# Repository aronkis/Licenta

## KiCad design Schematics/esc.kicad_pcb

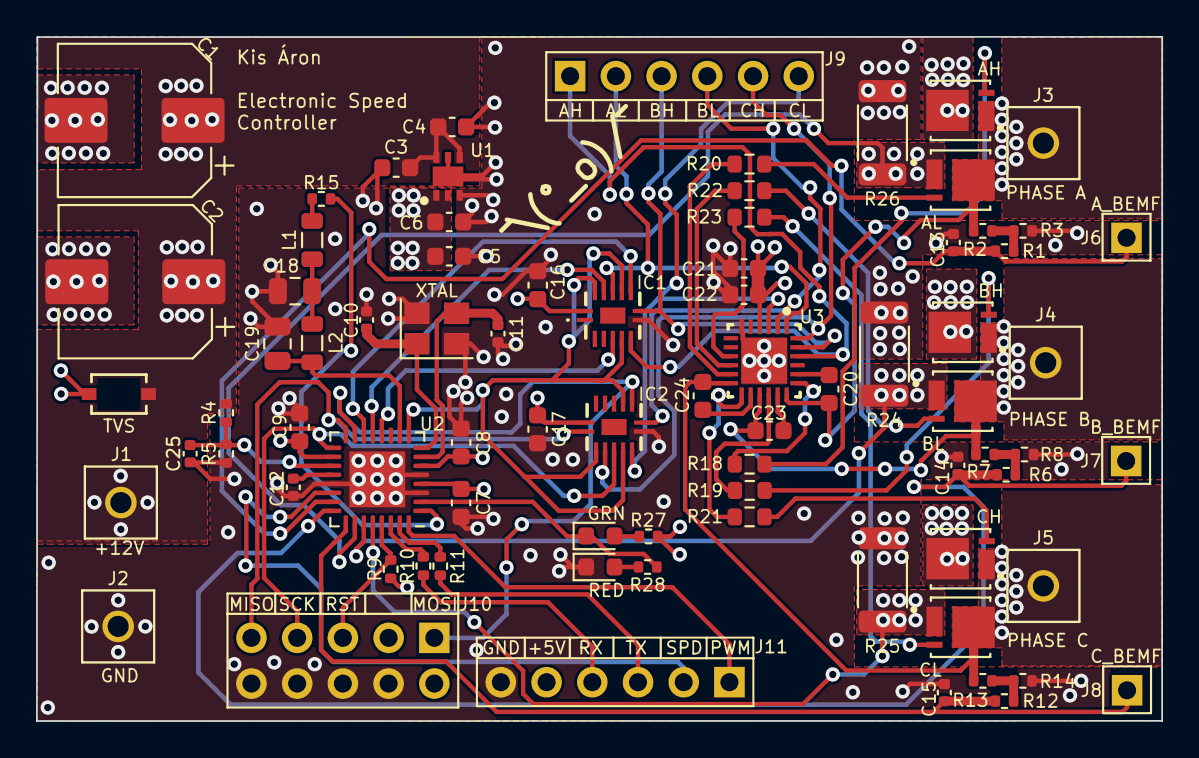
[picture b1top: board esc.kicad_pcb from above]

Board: 4 copper layers, 62.5 x 38.0 mm, 79 parts (0 on the bottom side), 61 nets.

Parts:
AH: BSZ0902NS
AL: BSZ0902NS
BH: BSZ0902NS
BL: BSZ0902NS
C1, C2: 470u; CP_Elec_8x10
C3, C4, C22: 1u; C_0603_1608Metric
C5, C6: 2.2u; C_0603_1608Metric
C7, C8, C9, C16, C17: 100n; C_0603_1608Metric
C10, C11: 22p; C_0402_1005Metric
C12, C25: 100n; C_0402_1005Metric
C13, C14, C15: 2.2n; C_0402_1005Metric
C18, C19: 47uF; C_0805_2012Metric
C20, C21, C23, C24: 0.1u; C_0603_1608Metric
CH: BSZ0902NS
CL: BSZ0902NS
GRN: LED; LED_0603_1608Metric
IC1, IC2: 74HCT08BQ,115; 74HCT08BQ115
J1, J2, J3, J4, J5: 8730
J6, J7, J8: Conn_01x01; PinHeader_1x01_P2.54mm_Vertical
J9, J11: Conn_01x06; PinHeader_1x06_P2.54mm_Vertical
J10: AVR-ISP-10; PinHeader_2x05_P2.54mm_Vertical
L1, L2: 100uH; L_0805_2012Metric
R1, R6, R9, R12: 10k; R_0402_1005Metric
R2, R4, R7, R13: 33k; R_0402_1005Metric
R3, R8, R14: 20k; R_0402_1005Metric
R5: 7.5k; R_0402_1005Metric
R10, R11: 1k; R_0402_1005Metric
R15: 30; R_0402_1005Metric
R18, R19, R20, R21, R22, R23: 15; R_0603_1608Metric
R24, R25, R26: 5m; R_2010_5025Metric
R27, R28: 300; R_0402_1005Metric
RED: LED; LED_0603_1608Metric
TVS: PTVS12VS1UTR_115; CR_1UTR_115_NEX
U1: TLV76750DRVx; SON65P200X200X80-7N
U2: ATmega328P-M; QFN-32-1EP_5x5mm_P0.5mm_EP3.1x3.1mm
U3: DRV8300DRGER; RGE0024B-IPC_C
XTAL: ECS-80-12-33-JGN-TR; Crystal_SMD_3225-4Pin_3.2x2.5mm

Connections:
+5V: C5.2, C6.2, C7.2, C8.2, C9.2, C16.1, C17.1, IC1.14 (VCC), IC2.14 (VCC), J10.2 (VCC), J11.5, R9.1, R27.1, U1.1 (OUT), U1.2 (SNS), U2.4 (VCC), U2.6 (VCC), U2.18 (AVCC)
+12V: AH.5_6_7_8, BH.5_6_7_8, C1.1, C2.1, C3.2, C4.2, C21.1, C22.2, CH.5_6_7_8, J1.1, R4.2, TVS.1, U1.4 (EN), U1.6 (IN), U3.4 (GVDD)
AH: IC1.4 (2A), U2.12 (PB0)
AH_PWM: IC1.6 (2Y), J9.1, U3.22 (INHA)
AL: IC1.12 (4A), U2.13 (PB1)
AL_PWM: IC1.11 (4Y), J9.2, U3.1 (INLA)
BH: IC1.9 (3A), U2.14 (PB2)
BH_PWM: IC1.8 (3Y), J9.3, U3.23 (INHB)
BL: IC2.9 (3A), J10.1 (MOSI), U2.15 (PB3)
BL_PWM: IC2.8 (3Y), J9.4, U3.2 (INLB)
CH: IC2.1 (1A), J10.9 (MISO), U2.16 (PB4)
CH_PWM: IC2.3 (1Y), J9.5, U3.24 (INHC)
CL: IC2.4 (2A), J10.7 (SCK), U2.17 (PB5)
CL_PWM: IC2.6 (2Y), J9.6, U3.3 (INLC)
COIL_A: AH.1_2_3, AL.5_6_7_8, C20.1, J3.1, R2.1, U3.18 (SHA)
COIL_A_BEMF: C13.2, J6.1, R1.1, U2.23 (PC0)
COIL_A_CURR: AL.1_2_3, R26.2, U2.26 (PC3)
COIL_B: BH.1_2_3, BL.5_6_7_8, C23.1, J4.1, R7.1, U3.15 (SHB)
COIL_B_BEMF: C14.2, J7.1, R6.1, U2.24 (PC1)
COIL_B_CURR: BL.1_2_3, R24.2, U2.27 (PC4)
COIL_C: C24.1, CH.1_2_3, CL.5_6_7_8, J5.1, R13.1, U3.12 (SHC)
COIL_C_BEMF: C15.2, J8.1, R12.1, U2.25 (PC2)
COIL_C_CURR: CL.1_2_3, R25.2, U2.28 (PC5)
COMP_REF_IN: C19.2, L2.2, U2.10 (PD6)
COMP_REF_OUT: R15.2, U2.1 (PD3)
GND: C1.2, C2.2, C3.1, C4.1, C5.1, C6.1, C7.1, C8.1, C9.1, C10.1, C11.1, C12.1, C13.1, C14.1, C15.1, C16.2, C17.2, C18.1, C19.1, C21.2, C22.1, C25.1, IC1.7 (GND_1), IC2.7 (GND_1), J2.1, J10.4 (GND), J10.6 (GND), J10.8 (GND), J10.10 (GND), J11.6, R3.1, R5.1, R8.1, R14.1, R24.1, R25.1, R26.1, RED.1 (K), TVS.2, U1.3 (GND), U1.5 (GND), U1.7 (PAD), U2.3 (GND), U2.5 (GND), U2.21 (GND), U2.33 (GND), U3.6 (GND), U3.25 (PowerPAD), XTAL.2, XTAL.4
LED: GRN.1 (K), R28.1, U2.2 (PD4)
unnamed: AH.4, R18.2
unnamed: AL.4, R20.2
unnamed: BH.4, R19.2
unnamed: BL.4, R22.2
unnamed: C18.2, L1.2, L2.1
unnamed: CH.4, R21.2
unnamed: CL.4, R23.2
unnamed: GRN.2 (A), R27.2
unnamed: L1.1, R15.1
unnamed: R1.2, R2.2, R3.2
unnamed: R6.2, R7.2, R8.2
unnamed: R12.2, R13.2, R14.2
unnamed: R28.2, RED.2 (A)
unnamed: C12.2, U2.20 (AREF)
unnamed: R10.2, U2.30 (PD0)
unnamed: R11.2, U2.31 (PD1)
unnamed: C20.2, U3.20 (BSTA)
unnamed: C23.2, U3.17 (BSTB)
unnamed: C24.2, U3.14 (BSTC)
unnamed: R18.1, U3.19 (GHA)
unnamed: R19.1, U3.16 (GHB)
unnamed: R21.1, U3.13 (GHC)
unnamed: R20.1, U3.11 (GLA)
unnamed: R22.1, U3.10 (GLB)
unnamed: R23.1, U3.9 (GLC)
PWM_IN: J11.1, U2.32 (PD2)
PWM_OUT: IC1.5 (2B), IC1.10 (3B), IC1.13 (4B), IC2.2 (1B), IC2.5 (2B), IC2.10 (3B), U2.9 (PD5)
RST: J10.5 (~RST), R9.2, U2.29 (~RESET/PC6)
RX: J11.4, R10.1
SPEED_REF: J11.2, U2.22 (ADC7)
TX: J11.3, R11.1
VBUS: C25.2, R4.1, R5.2, U2.19 (ADC6)
XTAL1: C11.2, U2.7 (XTAL1/PB6), XTAL.3
XTAL2: C10.2, U2.8 (XTAL2/PB7), XTAL.1

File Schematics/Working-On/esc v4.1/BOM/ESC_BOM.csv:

"Reference","Value","Datasheet","Footprint","Qty","DNP"
"8MHz1","ECS-80-12-33-JGN-TR","ECS-80-12-30BQ-JES-TR","Crystal:Crystal_SMD_3225-4Pin_3.2x2.5mm","1",""
"C1,C2","470u","~","Capacitor_SMD:CP_Elec_8x10","2",""
"C3,C4,C22","1u","~","Capacitor_SMD:C_0603_1608Metric","3",""
"C5,C6","2.2u","~","Capacitor_SMD:C_0603_1608Metric","2",""
"C7,C8,C9,C12,C16,C17","100n","~","-- mixed values --","6",""
"C10,C11","22p","~","Capacitor_SMD:C_0402_1005Metric","2",""
"C13,C14,C15","2.4n","~","Capacitor_SMD:C_0402_1005Metric","3",""
"C18,C19","47uF","~","Capacitor_SMD:C_0805_2012Metric","2",""
"C20,C21,C23,C24","0.1u","~","Capacitor_SMD:C_0603_1608Metric","4",""
"GRN1,RED1","LED","~","LED_SMD:LED_0603_1608Metric","2",""
"IC1,IC2","74HCT08BQ,115","https://assets.nexperia.com/documents/data-sheet/74HC_HCT08.pdf","74HCT08BQ115:74HCT08BQ115","2",""
"J1,J2,J3,J4,J5","8730","","8730:8730","5",""
"J6,J7,J8","Conn_01x01","~","Connector_PinHeader_1.00mm:PinHeader_1x01_P1.00mm_Vertical","3",""
"J9,J11","Conn_01x06","~","Connector_PinHeader_2.54mm:PinHeader_1x06_P2.54mm_Vertical","2",""
"J10","AVR-ISP-10"," ~","Connector_PinHeader_2.54mm:PinHeader_2x05_P2.54mm_Vertical","1",""
"L1,L2","100uH","~","Inductor_SMD:L_0805_2012Metric","2",""
"Q1,Q2,Q3,Q4,Q5,Q6","BSZ0902NS","","BSZ0902NS:BSZ0902NS","6",""
"R1,R3,R5,R6,R8,R9,R12,R14","10k","~","Resistor_SMD:R_0402_1005Metric","8",""
"R2,R4,R7,R13","33k","~","Resistor_SMD:R_0402_1005Metric","4",""
"R10,R11","1k","~","Resistor_SMD:R_0402_1005Metric","2",""
"R15","30","~","Resistor_SMD:R_0402_1005Metric","1",""
"R16,R17","300","~","Resistor_SMD:R_0402_1005Metric","2",""
"R18,R19,R20,R21,R22,R23","15","~","Resistor_SMD:R_0603_1608Metric","6",""
"R24,R25,R26","5m","~","Resistor_SMD:R_2010_5025Metric","3",""
"TVS1","PTVS12VS1UTR_115","PTVS12VS1UTR_115","PTVS12VS1UTR-115:CR_1UTR_115_NEX","1",""
"U1","TLV76750DRVx","www.ti.com/lit/gpn/TLV767","TLV76750DRVR:SON65P200X200X80-7N","1",""
"U2","ATmega328P-M","http://ww1.microchip.com/downloads/en/DeviceDoc/ATmega328_P%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","Package_DFN_QFN:QFN-32-1EP_5x5mm_P0.5mm_EP3.1x3.1mm","1",""
"U3","DRV8300DRGER","DRV8300DRGER","DRV8300DRGER:RGE0024B-IPC_C","1",""

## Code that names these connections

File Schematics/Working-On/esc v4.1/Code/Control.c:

#include "Arduino.h"

const uint8_t max_pwm_adr = 0x00;
const uint8_t min_pwm_adr = 0x02;

const uint8_t pwm_start_value = 35;
const uint8_t pwm_min_value = 35;
const uint8_t pwm_max_value = 255;
uint8_t motor_speed = 0;
uint8_t pwm_pin_change = 0;


uint64_t pwm_end = 0;
uint64_t pwm_start = 0;

const uint16_t min_pwm = 1000;
const uint16_t max_pwm = 2000;
uint16_t motor_off_timer = 1000;
uint16_t pwm_input = 550;
uint16_t soft_start_timer = 2200;

static bool motor_enabled = false;
static uint8_t sequence_step = 0;

void setup()
{  
  // The pins for the MOSFET drivers are PB1, PB2, PB3, PD2, PD3 and PD4
  DDRB  |= B00001110;           // Configure pins PB1, PB2, PB3 as output (CH, BH, AH)
  PORTB &= B00000000;           // Pins 0 to 7 set to LOW
  DDRD  |= B00011100;           // Configure pin PD2, PD3, PD4 as output (CL, BL, AL)
  PORTD &= B00000000;           // Pins 0 to 7 set to LOW

  // Timer0
  TCCR1A = 0;
  TCCR1B = 0x01; // no prescaling

  // Timer1
  TCCR2A = 0;
  TCCR2B = 0x01; // no prescaling

  // Comparator on pin PD6
  ACSR   = 0x10;             // enable comparator interrupt

  // Set PB0 (PWM in) to trigger interrupt (we use this to read PWM input)
  PCICR  |= (1 << PCIE0);    // enable PCMSK0 scan, PWM_IN (PB0), which is PCIE0 in PCICR register.                                           
  PCMSK0 |= (1 << PCINT0);   // Set pin PB0 to trigger an interrupt on state change. 

  // For the comparator to be functional the ADC has to be disabled.
  ADCSRA = (0 << ADEN);     // Disable the ADC
  ADCSRB = (1 << ACME);     // MUX select for negative input of comparator
}

void soft_start()
{
  set_pwm(pwm_start_value);
  soft_start_timer = 2000;

  while(soft_start_timer > 500) {
    delayMicroseconds(soft_start_timer);
    set_next_step();
    sequence_step++;
    sequence_step %= 6;
    soft_start_timer -= 10;
  }

  motor_speed = pwm_start_value;    //??
  ACSR |= 0x08;                    // Enable analog comparator interrupt 
}

void motor_stop()
{
  if(!motor_off_timer) // to assure that the motor doesn't stop immediately
  {
    motor_enabled = false;
    ACSR   = 0x10;            // Disable and clear (flag bit) analog comparator interrupt
    motor_off_timer = 1000;
    PORTD = B00000000;
    PORTB = B00000000;
    TCCR1A =  0;   
    TCCR2A =  0;            
  }
  motor_off_timer = motor_off_timer - 1;       
}

void loop() {
  // if the PWM input is higher than a given threshold we start the motor
  if(pwm_input > min_pwm + 40)
  {
    motor_enabled = true;    
    motor_off_timer = 1000;
  }

  if(motor_enabled)
  {  
    soft_start();
    while(motor_enabled) 
    {
      pwm_input = constrain(pwm_input, min_pwm, max_pwm);
      motor_speed = map(pwm_input, min_pwm, max_pwm, pwm_min_value, pwm_max_value);
      set_pwm(motor_speed);
      if(pwm_input < min_pwm) // stop the motor
      {
        motor_stop();
      }
    }
  } 
} 

// Setting the timers to the PWM value
void set_pwm(byte pwm_value){
  OCR1A  = pwm_value;                   // Set pin PB1 PWM duty cycle
  OCR1B  = pwm_value;                   // Set pin PB2 PWM duty cycle
  OCR2A  = pwm_value;                   // Set pin PB3 PWM duty cycle
}

// Detecting the 0 crossing on falling and rising edges.
void BEMF_A_RISING(){  
  ADMUX = 2;                // Select PC2 as comparator negative input
  ACSR |= 0x03;             // Set interrupt on rising edge*/
}

void BEMF_A_FALLING(){
  ADMUX = 2;                // Select PC2 as comparator negative input
  ACSR &= ~0x01;            // Set interrupt on falling edge*/
}

void BEMF_B_RISING(){
  ADMUX = 0;                // Select PC0 as comparator negative input
  ACSR |= 0x03;             // Set interrupt on rising edge
}

void BEMF_B_FALLING(){
  ADMUX = 0;                // Select PC0 as comparator negative input
  ACSR &= ~0x01;            // Set interrupt on falling edge*/
}

void BEMF_C_RISING(){
  ADMUX = 1;                // Select PC1 as comparator negative input
  ACSR |= 0x03;             // Set interrupt on rising edge
}

void BEMF_C_FALLING(){
  ADMUX = 1;                // Select PC1 as comparator negative input
  ACSR &= ~0x01;            // Set interrupt on falling edge
}

// ACO indicates the output of the comparator, when AIN0 (PD6 - Virtual 0) voltage is 
// higher than the negative pin voltage then the ACO bit is set, otherwise it is clear.
ISR (ANALOG_COMP_vect) {
  for(int i = 0; i < 10; i++) {
    if(sequence_step & 1)             // If step = odd (0001, 0011, 0101) 1, 3 or 5
    {
      if(!(ACSR & 0x20)) i -= 1;      // ACO = 0 (Analog Comparator Output = 0) -> BEMF > Virtual 0
    }
    else                              // else if step is 0, 2 or 4
    {
      if((ACSR & 0x20)) i -= 1;       // ACO = 1 (Analog Comparator Output = 1) -> BEMF < Virtual 0
    }
  }
  set_next_step();                    // set the next step of the sequence
  sequence_step++;                    // increment step by 1, next part of the sequence of 6
  sequence_step %= 6;                 // If step > 5 (equal to 6) then step = 0 and start over
}

void set_next_step(){        
  switch(sequence_step){
    case 0:
      AH_BL();
      BEMF_C_RISING();
      break;
    case 1:
      AH_CL();
      BEMF_B_FALLING();
      break;
    case 2:
      BH_CL();
      BEMF_A_RISING();
      break;
    case 3:
      BH_AL();
      BEMF_C_FALLING();
      break;
    case 4:
      CH_AL();
      BEMF_B_RISING();
      break;
    case 5:
      CH_BL();
      BEMF_A_FALLING();
      break;
  }
}

/*On each step we change the digital pins to be HIGH or LOW or to be PWM or no-PWM 
depending on which step of the sequence we are*/
void AH_BL(){
  PORTD  = B00001000;     
  TCCR1A =  0;         
  TCCR2A =  0x81;         // OC2A - compare match noninverting mode, downcounting, PWM 8-bit      
}

void AH_CL(){
  PORTD  = B00000100;      
  TCCR1A =  0;         
  TCCR2A =  0x81;         // OC2A - compare match noninverting mode, downcounting, PWM 8-bit      
}

void BH_CL(){
  PORTD  = B00000100;      
  TCCR2A =  0;            
  TCCR1A =  0x21;         // OC1B - compare match noninverting mode, downcounting, PWM 8-bit 
}

void BH_AL(){  
  PORTD  = B00010000;      
  TCCR2A =  0;                  
  TCCR1A =  0x21;         // OC1B - compare match noninverting mode, downcounting, PWM 8-bit 
}

void CH_AL(){ 
  PORTD  = B00010000;       
  TCCR2A =  0;          
  TCCR1A =  0x81;         // OC1A - compare match noninverting mode, downcounting, PWM 8-bit 
}

void CH_BL(){  
  PORTD  = B00001000;        
  TCCR2A =  0;             
  TCCR1A =  0x81;         // OC1A - compare match noninverting mode, downcounting, PWM 8-bit
}

/* This is the interruption routine on pin change
   in this case for digital pin PB0 which is the PWM input */
ISR(PCINT0_vect){
  // First we take the current time in micro seconds using the micros() function
  pwm_end = micros();

  if(PINB & 0x01){                                   // We make an AND with the pin state register, We verify if pin 8 is HIGH
    if(pwm_pin_change == 0){                         // If the last state was 0, then we have a state change...
      pwm_pin_change = 1;                            // Store the current state into the last state for the next loop
      pwm_start = pwm_end;                           // Set counter_1 to current value.
    }
  }
  else if(pwm_pin_change == 1){                      // If pin PB0 is LOW and the last state was HIGH then we have a state change      
    pwm_pin_change = 0;                              // Store the current state into the last state for the next loop
    pwm_input = pwm_end - pwm_start;                 // We make the time difference. PWM_INPUT is current_time - counter_1 in micro-seconds.
  }
}

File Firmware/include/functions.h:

#ifndef _FUNCTIONS_H_
#define _FUNCTIONS_H_

#include <stdint.h>

#define FALSE 0
#define TRUE  (!FALSE)

#define SYSTEM_CLOCK_FREQUENCY 8000000
#define BASE_PWM_FREQUENCY 20000
#define PWM_TOP_VALUE (SYSTEM_CLOCK_FREQUENCY / BASE_PWM_FREQUENCY / 2) //200
#define PWM_MIN_VALUE  30
#define PWM_START_VALUE 90
#define PWM_MAX_VALUE   (PWM_TOP_VALUE - 1)
#define DELAY_MULTIPLIER 10

// Digital output pins
#define AH PB0
#define AL PB1
#define BH PB2
#define BL PB3
#define CH PB4
#define CL PB5

#define DRIVE_REG DDRB
#define DRIVE_PORT PORTB

#define PWM_PIN PD5
#define LED_PIN PD4

// Commutation steps
#define AH_BL ((SET_BIT(AH)) | SET_BIT(BL))
#define AH_CL ((SET_BIT(AH)) | SET_BIT(CL))
#define BH_CL ((SET_BIT(BH)) | SET_BIT(CL))
#define BH_AL ((SET_BIT(BH)) | SET_BIT(AL))
#define CH_AL ((SET_BIT(CH)) | SET_BIT(AL))
#define CH_BL ((SET_BIT(CH)) | SET_BIT(BL))

// ADC settings
#define ZC_DETECTION_THRESHOLD (zcThresholdVoltage)
#define ADC_COIL_A_PIN  0x00
#define ADC_COIL_B_PIN  0x01
#define ADC_COIL_C_PIN  0x02
#define ADC_CURR_A_PIN  0x03
#define ADC_CURR_B_PIN  0x04
#define ADC_CURR_C_PIN  0x05
#define ADC_VBUS_PIN    0x06
#define ADC_SPD_REF_PIN 0x07
#define ADC_REF_SELECTION ((0 << REFS1) | (1 << REFS0)) // Using AVcc as the AREF
#define ADC_RES_ADJUST (1 << ADLAR) // 8 bit precision
#define ADC_PRESCALER_8 ((0 << ADPS2) | (1 << ADPS1) | (1 << ADPS0)) // limit the ADC clock to 1 MHz
#define ADC_TRIGGER_SOURCE ((0 << ADTS2) | (0 << ADTS1) | (0 << ADTS0)) // Free running conversion;
#define ADMUX_COIL_A  (ADC_REF_SELECTION | ADC_RES_ADJUST | ADC_COIL_A_PIN)
#define ADMUX_COIL_B  (ADC_REF_SELECTION | ADC_RES_ADJUST | ADC_COIL_B_PIN)
#define ADMUX_COIL_C  (ADC_REF_SELECTION | ADC_RES_ADJUST | ADC_COIL_C_PIN)
#define ADMUX_CURR_A  (ADC_REF_SELECTION | ADC_RES_ADJUST | ADC_CURR_A_PIN)
#define ADMUX_CURR_B  (ADC_REF_SELECTION | ADC_RES_ADJUST | ADC_CURR_B_PIN)
#define ADMUX_CURR_C  (ADC_REF_SELECTION | ADC_RES_ADJUST | ADC_CURR_C_PIN)
#define ADMUX_SPD_REF (ADC_REF_SELECTION | ADC_RES_ADJUST | ADC_SPD_REF_PIN)
#define ADMUX_VBUS    (ADC_REF_SELECTION | ADC_RES_ADJUST | ADC_VBUS_PIN)

// Variables used for the current measure
#define ADC_RESOLUTION 256
#define ADC_REFERENCE 5000  // [mV]
#define SHUNT_RESISTANCE 20 // [mOhm]
#define CURRENT_LIMIT 10000 // [mA]

// BEMF signal options
#define RISING 1
#define FALLING 0

#define START_UP_COMMS 6
#define NUMBER_OF_STEPS 6
#define STARTUP_DELAY 15000

#define SET_BIT(bitPos) (1 << bitPos)
#define CLEAR_BIT(bitPos) (~(1 << bitPos))
#define CLEAR_REGISTER(reg) (reg &= ~reg)
#define CLEAR_INTERRUPT_FLAGS(reg) (reg = reg)
#define RED_LED (PORTD |= SET_BIT(PD4))
#define GREEN_LED (PORTD &= CLEAR_BIT(PD4))

enum ADC_STATE
{
     ADC_BEMF_READ = 0,
     ADC_SPEED_REFERENCE_READ
};

enum PROGRAM_STATE
{
    STARTUP = 0,
    RUNNING,
    RESTART
};

volatile uint8_t nextStep;
volatile uint8_t nextPhase;
volatile uint8_t zeroCrossPolarity;
volatile uint8_t zcThresholdVoltage;
volatile uint8_t speedReference;
volatile uint8_t speedReferenceSave;
volatile uint8_t backEMFFound;
volatile uint8_t motorStarted;
volatile uint16_t thirtyDegreeTime;
volatile uint16_t motorStartupDelay;
volatile uint16_t motorStopCounter;
volatile enum ADC_STATE commutationState;
enum PROGRAM_STATE programState;
uint8_t debugMode;
uint16_t electricalSpeed;

uint8_t driveTable[NUMBER_OF_STEPS];
uint8_t ADMUXTable[NUMBER_OF_STEPS];
uint8_t currentTable[NUMBER_OF_STEPS];
uint16_t startupDelays[START_UP_COMMS];

void initPorts(void);
void initTimers(void);
void initADC(void);
void generateTables(void);
void startMotor(void);
void stopMotor(void);
void checkForMotorStop(void);
void checkForStartMotor(void);
void startupDelay(uint64_t time);
void setup(void);
void runMotor(void);
uint8_t checkForZeroCrossPolarity(void);
uint16_t getElectricalSpeed(void);

#endif // _FUNCTIONS_H_

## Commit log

2024-04-26 Saving files to git
2024-04-28 BEMF_Filter config.
2024-04-29 New connectors, and BEMF Filter.
2024-04-30 VIA update
2024-05-01 swaped PWM_IN & Comp_Ref_Out, vias finished
2024-05-04 Added pins for the BACK-EMFs and PWM Control signals
2024-05-05 Changed 8MHz to XTAL (might use 16MHz)
2024-05-07 Added VBUS measurment.
2024-05-07 Ready to order(?)
2024-05-08 Ready to order.
2024-05-09 2 Layers Current Resistor connection.
2024-05-10 Changing the VD Resistors to 3.33k.
2024-05-11 Adding the firmware from a different repo.
2024-05-13 redoing the adc triggers/interupt routine.
2024-05-17 Interupt updates.
2024-05-23 Timer1 calibration.
2024-05-26 Timer2 setup.
2024-05-30 Saving current progress with adc interrupt.
2024-06-18 Motor speed stabilized.
2024-06-23 Before adding motor stop/restart functionality.
2024-06-23 After restart does not read the VBUS.
2024-06-23 Plot function.
2024-06-24 Plotting Duty cycle and rotation speed.
2024-06-24 Done.
2024-06-25 Cleaning up.
2024-06-27 V1.0
2024-06-30 Removing zone identifiers and some code cleanup.
2024-07-01 Stall detection and speed calculation update.
2024-07-02 Cleanup and modifying the speed calculation.
2024-07-03 Sampling option and removing unused components.
2024-07-08 Startup lock to 150 [ms].
